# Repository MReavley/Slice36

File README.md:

# ThinSlice36 Minimalist Split Keyboard

Modification of the Slice36 for thinness. 

## Modifications from upstream:

- Low-profile switches (choc v1)
- Choc spacing
- Reversible PCB, designed around 0805 smd components to be hand-solderable or using an assembly service.
- Built around the Seeeduino Xiao RP2040(hooray USB-C), using KMK.  
- No plate

## BOM
- Seeeduino Xiao RP2040 x2
- 1N4148WS Diodes (SOD-323) x36
- PJ320D TRRS jacks x2
- 0805 10k resistors x6 (additional footprints R4-R7 for I2C communication for splits, may not be required)
- Kailh Choc v1 style switches x36
- Keycaps x36
- TRRS cable  

## Things to note if you want to build one:

- IMPORTANT: The xiao on the right half (master) is to be soldered with the LED/chip facing up, and the left half (slave) upside down, so that the pinout still matches the flipped PCB.
- Upstream uses 8mm rubber feet that are 1.5mm tall which are just about tall enough, but taller rubber feet might be better.
- TRRS jacks for the split are connected to the I2C pins on the Xiao board. Since KMK uses UART for split communications, I used PIO on the RP2040 to change those pins to UART, but I don't know what your options are on the SAMD21 version if you wish to use UART on those.
- Upstream prototype found that the SAMD21 version of the Xiao required external pullups on the I2C lines and added those to this board, but has not tested if they are necessary yet. Currently using 10k resistors (to simplify BOM), and it is working fine.

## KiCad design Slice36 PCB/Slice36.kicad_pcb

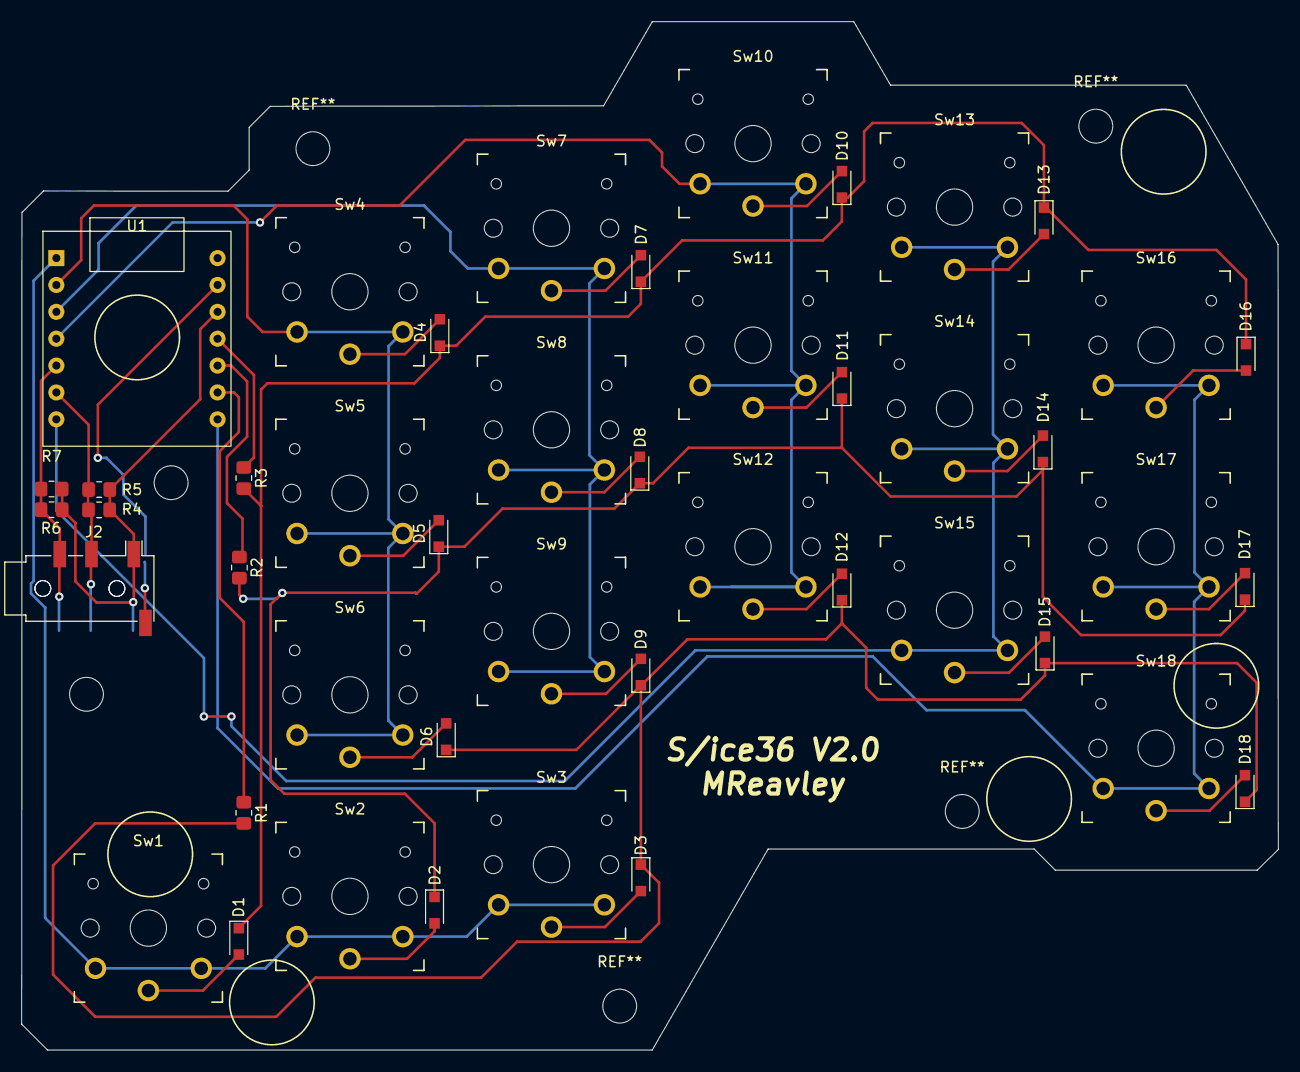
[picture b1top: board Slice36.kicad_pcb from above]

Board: 2 copper layers, 118.8 x 97.2 mm, 46 parts (1 on the bottom side), 34 nets.

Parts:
D1, D2, D3, D4, D5, D6, D7, D8, D9, D10, D11, D12, D13, D14, D15, D16, D17, D18: 1N4148WS; D_SOD-323_HandSoldering
J1, J2: AudioJack4; Jack_3.5mm_PJ320D_Horizontal
R1, R2, R3, R4, R5, R6, R7: 10k; R_0805_2012Metric_Pad1.20x1.40mm_HandSolder
Sw1, Sw2, Sw3, Sw4, Sw5, Sw6, Sw7, Sw8, Sw9, Sw10, Sw11, Sw12, Sw13, Sw14, Sw15, Sw16, Sw17, Sw18: choc_v1_dbl; SW_PG1350_reversible
U1: SeeeduinoXIAO; Xiao THT V1

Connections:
unnamed: D1.1 (K), D4.1 (K), D7.1 (K), D10.1 (K), D13.1 (K), D16.1 (K), R3.2
unnamed: D1.2 (A), Sw1.1 (NE)
unnamed: D2.2 (A), Sw2.1 (NE)
unnamed: D3.2 (A), Sw3.1 (NE)
unnamed: D4.2 (A), Sw4.1 (NE)
unnamed: D5.2 (A), Sw5.1 (NE)
unnamed: D6.2 (A), Sw6.1 (NE)
unnamed: D7.2 (A), Sw7.1 (NE)
unnamed: D8.2 (A), Sw8.1 (NE)
unnamed: D9.2 (A), Sw9.1 (NE)
unnamed: D10.2 (A), Sw10.1 (NE)
unnamed: D2.1 (K), D5.1 (K), D8.1 (K), D11.1 (K), D14.1 (K), D17.1 (K), R2.2
unnamed: D11.2 (A), Sw11.1 (NE)
unnamed: D3.1 (K), D6.1 (K), D9.1 (K), D12.1 (K), D15.1 (K), D18.1 (K), R1.2
unnamed: D12.2 (A), Sw12.1 (NE)
unnamed: D13.2 (A), Sw13.1 (NE)
unnamed: D14.2 (A), Sw14.1 (NE)
unnamed: D16.2 (A), Sw16.1 (NE)
unnamed: D17.2 (A), Sw17.1 (NE)
unnamed: D18.2 (A), Sw18.1 (NE)
unnamed: J1.R1, J2.R1, R4.2, R5.2, U1.6 (PA9_A5_D5_SCL)
unnamed: J1.R2, J2.R2, R6.2, R7.2, U1.5 (PA8_A4_D4_SDA)
unnamed: J1.S, J2.S, U1.13 (GND)
unnamed: J1.T, J2.T, R4.1, R5.1, R6.1, R7.1, U1.12 (3V3)
unnamed: R1.1, U1.9 (PA7_A8_D8_SCK)
unnamed: R2.1, U1.10 (PA5_A9_D9_MISO)
unnamed: R3.1, U1.11 (PA6_A10_D10_MOSI)
unnamed: Sw1.2 (NW), Sw2.2 (NW), Sw3.2 (NW), U1.1 (PA02_A0_D0)
unnamed: Sw4.2 (SW), Sw5.2 (SW), Sw6.2 (NW), U1.2 (PA4_A1_D1)
unnamed: Sw7.2 (NW), Sw8.2 (NW), Sw9.2 (NW), U1.3 (PA10_A2_D2)
unnamed: Sw10.2 (NW), Sw11.2 (NW), Sw12.2 (NW), U1.4 (PA11_A3_D3)
unnamed: D15.2 (A), Sw15.1 (NE)
unnamed: Sw13.2 (SW), Sw14.2 (SW), Sw15.2 (SW), U1.7 (PB08_A6_D6_TX)
unnamed: Sw16.2 (SW), Sw17.2 (NW), Sw18.2 (NW), U1.8 (PB09_A7_D7_RX)

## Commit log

2022-04-22 Rename Slice36 Plate.dxf to Plate/Slice36 Plate.dxf
2022-04-22 Rename Slice36.kicad_pcb to LiCad/Slice36.kicad_pcb
2022-08-30 Delete adafruit_pioasm.mpy
    Removing to reduce confusion, just use the folders directly
2022-08-30 Delete code.py
    Removed to reduce confusion, just directly copy paste the contents of the left and right folders into the respective keyboards
2022-08-30 Delete kb.py
    Removed to reduce confusion, just refer to the folders directly
2023-02-08 Convert switchs to Kailh Choc V1, update routes
2023-02-08 Update README.md
    Fixed markdown.
